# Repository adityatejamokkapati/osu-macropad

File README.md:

osu-macropad 🎮

A custom USB macropad designed in KiCad for osu!, gaming shortcuts, and everyday productivity.

Features

5 mechanical keyboard switches for programmable shortcuts

Arduino Nano RP2040 Connect as the controller

OLED screen for displaying status and modes

Planned rotary encoder for volume control and navigation

Custom PCB designed using KiCad

Hardware

Arduino Nano RP2040 Connect

5 MX-style mechanical switches (Gateron Milky Yellow Pro planned)

4-pin OLED display

Rotary encoder (replacement model to be selected)

Custom PCB

PCB Design

The schematic and PCB are currently under development. The schematic has passed KiCad's Electrical Rules Checker, but the physical PCB still needs footprint verification, routing, and design checks.

Firmware

See [`firmware/`](firmware/) — Arduino (Earle Philhower `arduino-pico` core + TinyUSB) firmware, verified to compile for the Nano RP2040 Connect.

* 5 keys (D0/D6/D7/D8/D5) as NKRO HID keyboard, 1 ms scan, 5 ms debounce
* EC11 encoder (D2/D3 + button D4): volume / layer control, short-press = mute, long-press = layer cycle
* SSD1306 OLED (SDA/A4, SCL/A5) showing layer, key state, CPS, volume
* 3 layers (osu! / MEDIA / WORK) persisted to LittleFS; edit the map in `firmware/keymap.h`

Build: open `firmware/firmware.ino` in Arduino IDE 2.x (board "Arduino Nano RP2040 Connect", USB Stack "Adafruit TinyUSB") or see `firmware/README.md` for `arduino-cli` commands.

Project Status

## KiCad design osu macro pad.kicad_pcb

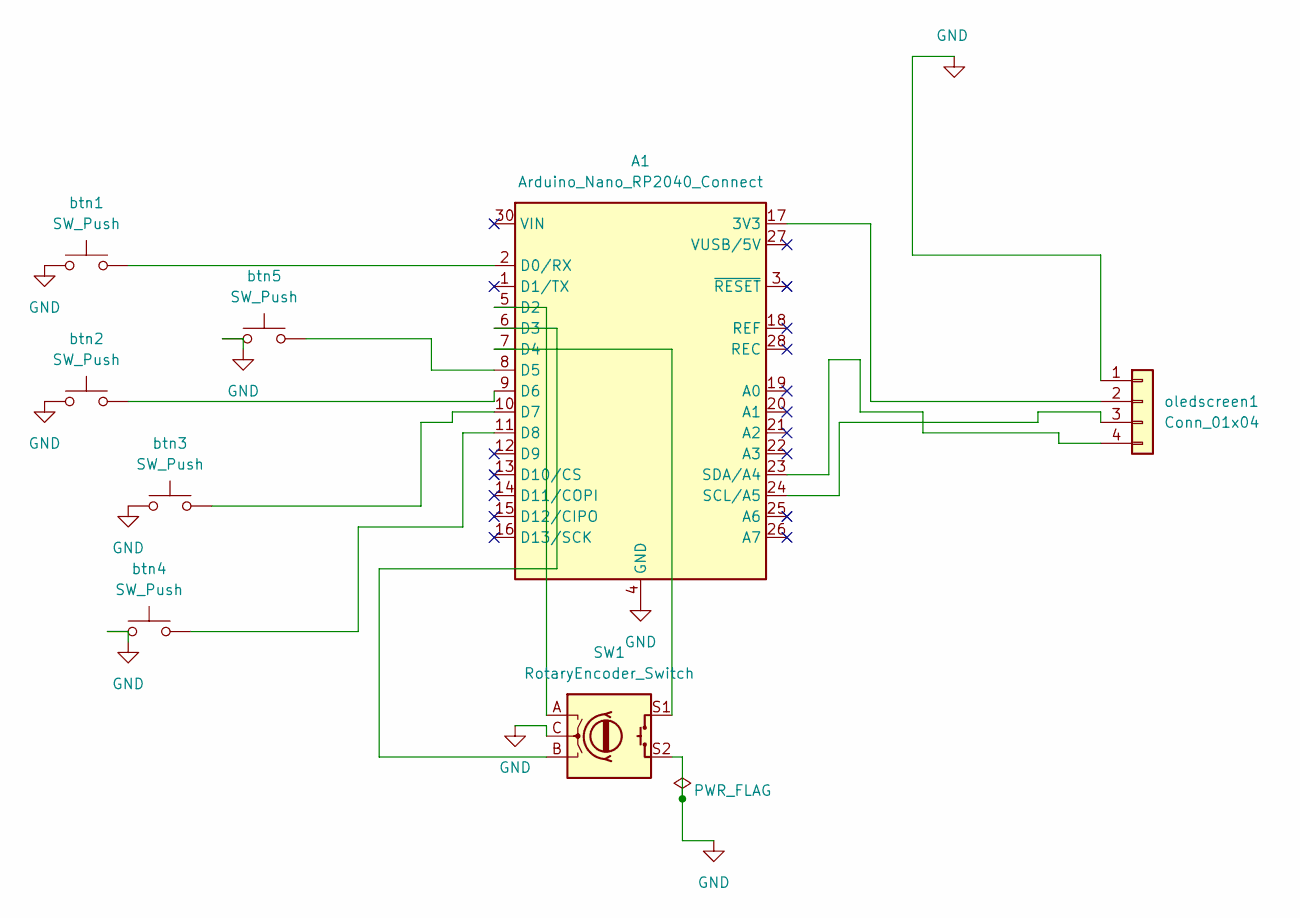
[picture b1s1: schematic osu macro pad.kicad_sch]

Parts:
A1: Arduino_Nano_RP2040_Connect; Arduino_Nano
SW1: RotaryEncoder_Switch; RotaryEncoder_Alps_EC11E-Switch_Vertical_H20mm
btn1, btn2, btn3, btn4, btn5: SW_Push; SW_Cherry_MX_1.00u_PCB
oledscreen1: Conn_01x04; PinSocket_1x04_P2.54mm_Vertical

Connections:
GND: A1.4 (GND), A1.29 (GND), SW1.C, SW1.S2, btn1.1, btn2.1, btn3.1, btn4.1, btn5.1, oledscreen1.1
unnamed: A1.17 (3V3), oledscreen1.2
unnamed: A1.2 (D0/RX), btn1.2
unnamed: A1.5 (D2), SW1.A
unnamed: A1.6 (D3), SW1.B
unnamed: A1.7 (D4), SW1.S1
unnamed: A1.8 (D5), btn5.2
unnamed: A1.9 (D6), btn2.2
unnamed: A1.10 (D7), btn3.2
unnamed: A1.11 (D8), btn4.2
unnamed: A1.24 (SCL/A5), oledscreen1.3
unnamed: A1.23 (SDA/A4), oledscreen1.4

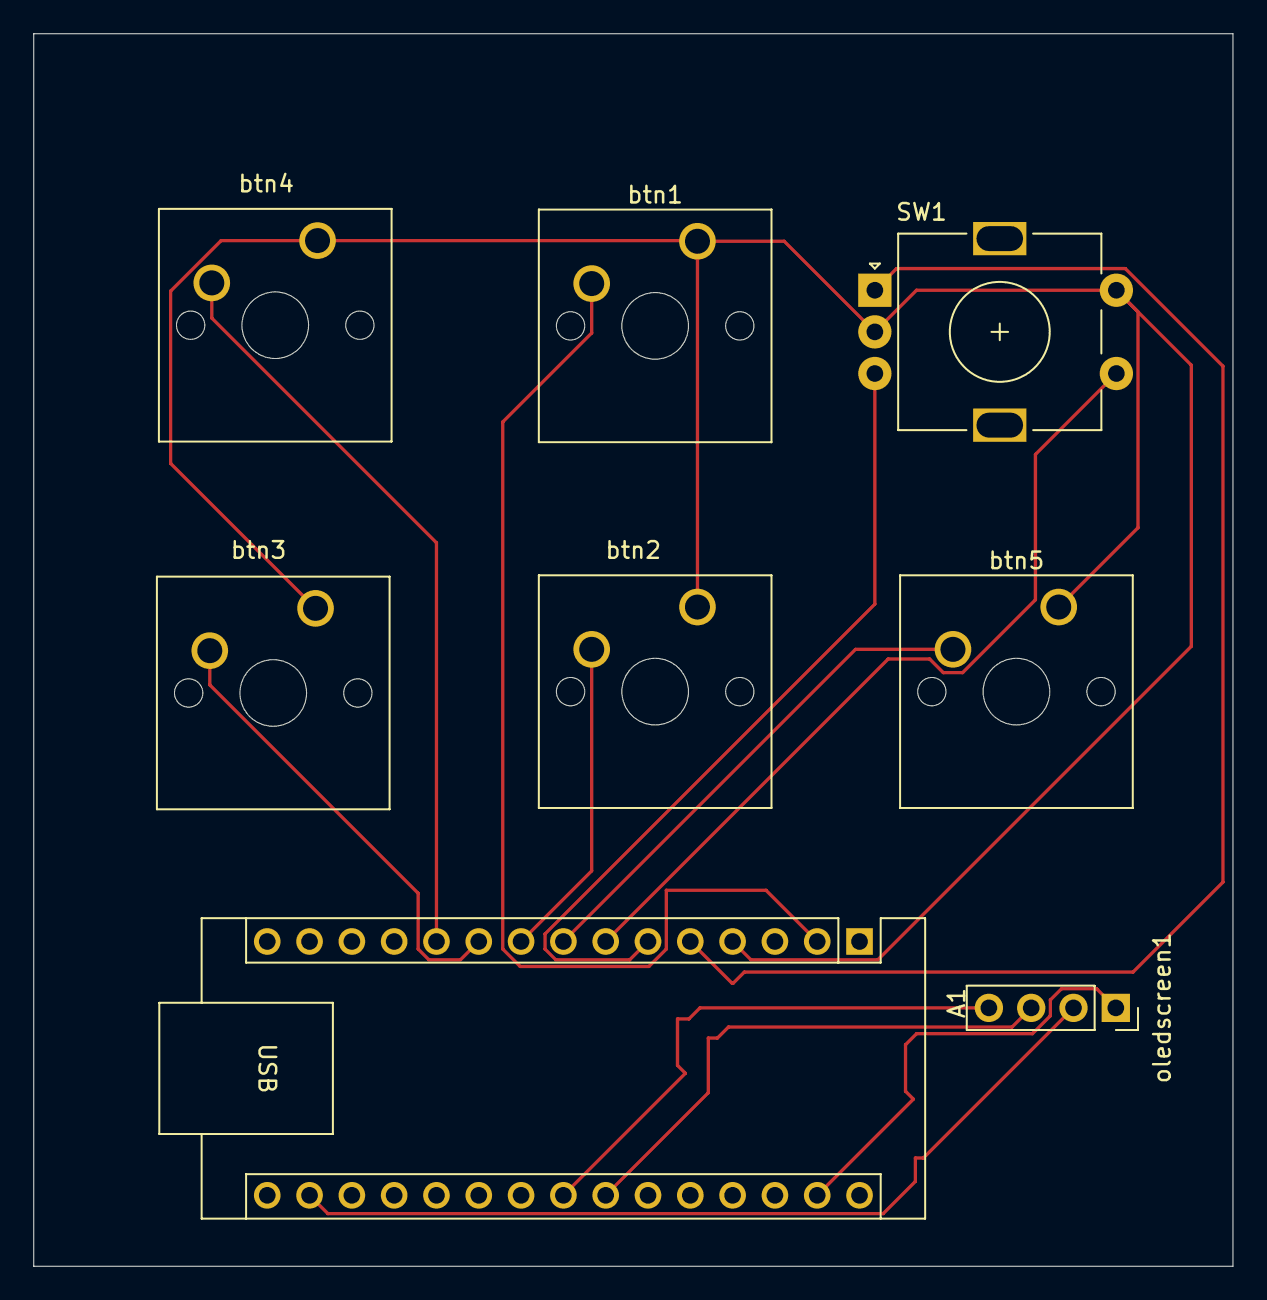
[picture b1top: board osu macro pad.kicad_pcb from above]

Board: 2 copper layers, 72.0 x 74.0 mm, 8 parts (0 on the bottom side), 12 nets.
